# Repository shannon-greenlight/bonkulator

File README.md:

# Bonkulator
# The Bonkulator has been replaced by Thor's Arsenal

The Bonkulator is a Eurorack module that fits into a 3U x 14HP slot. It features 8 programmable outputs and 6 programmable inputs. The front-panel user controls consist of a 128×64 pixel 2-color OLED display, a rotary encoder for adjusting parameters and a button for each trigger and output.

# main_board, panel

These repos contain the materials needed to construct the Bonkulator main board and the front panel.
The files are for KiCAD 6.0. Go to the Greenlight Kicad repo to get the needed libraries.
The gerber files work with JLCPC and will most likely work with other board manufacturers.

Assembly instructions are in main_board\fab\bonkulator_assembly.docx.

When using the JLCPCB assembly service, the BOM is split into 3 parts.

- bom/lcsc/bonkulator_bom.xlsx : The parts to be assembled by JLCPCB
- bom/digi-key/bonkulator_bom.xlsx : The remaining parts to be assembled by user
- bom/other/other_bom.xlsx : The parts that must be bought from sources other than JLCPCB and Digi-Key

Also, when an assembly service is used, a component position file is required. This file's path is: fab/Bonkulator_cpl.xlsx

notes: The bom and cpl files are auto-generated from the csv BOM files produced by KiCAD. You will need to refresh the data when changes to the schematic that affect the BOM or changes to the board layout occur.
If they exist, the extra parts and additional data fields that appear on the schematic help to produce the different BOM files. They must be maintained for these BOMs to come out right.

# code

This repository contains the elements needed to build code for the Bonkulator.

# BonkDaddy

The Bonk Daddy is an addition to the Bonkulator that provides these benefits:

- Front Panel USB access
- Power sensing shuts off USB to Arduino when synth power is off
- Reset switch
- USB Power indicator
- Trig In indicators
- Boot Loader indicator
- Extremely useful to those who use Terminal Remote mode

The folder structure of the Bonk Daddy is similar to the Bonkulator Hardware folder, main_board. Currently there is no support for assembly service.

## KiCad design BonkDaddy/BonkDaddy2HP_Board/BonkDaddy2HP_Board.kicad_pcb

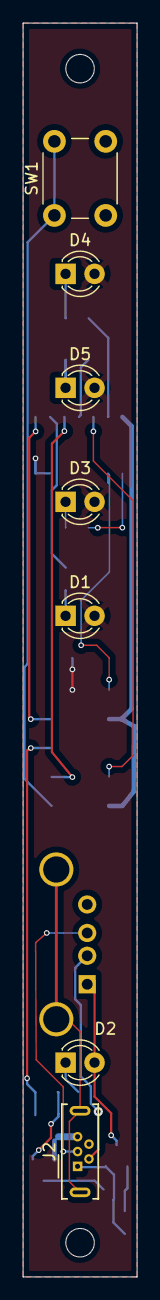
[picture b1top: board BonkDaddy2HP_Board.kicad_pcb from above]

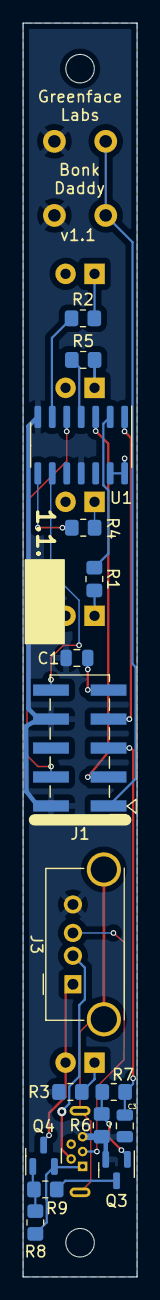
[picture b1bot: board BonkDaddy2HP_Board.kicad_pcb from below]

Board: 2 copper layers, 10.0 x 110.0 mm, 25 parts (16 on the bottom side), 25 nets.

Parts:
C1, C3: 1uF; C_0805_2012Metric
D1: RED LED; LED_D3.0mm
D2, D4: GREEN LED; LED_D3.0mm
D3: YELLOW LED; LED_D3.0mm
D5: BLUE LED; LED_D3.0mm
H1, H2: MountingHole; MountingHole_2.5mm
J1: EXP; PinHeader_2x05_P2.54mm_Vertical_SMD
J2: USB_B_Micro; USB_Micro-B_Wuerth_614105150721_Vertical
J3: USB_A; USB_A_Amphenol_UE27AE54100_Vertical
Q3: 2N7002; SOT-23
Q4: MMBT3906; SOT-23
R1, R2, R4, R5: 620; R_0805_2012Metric_Pad1.20x1.40mm_HandSolder
R3: 1K; R_0805_2012Metric_Pad1.20x1.40mm_HandSolder
R6, R9: 10K; R_0805_2012Metric_Pad1.20x1.40mm_HandSolder
R7, R8: 30K; R_0805_2012Metric_Pad1.20x1.40mm_HandSolder
SW1: Reset; SW_PUSH_6mm
U1: 74AHC14; SOIC-14_3.9x8.7mm_P1.27mm

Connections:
+3V3: C1.1, D1.2 (A), D3.2 (A), D4.2 (A), D5.2 (A), J1.9, U1.13, U1.14 (VCC)
+12V: C3.1, J1.5, R7.2
GND: C1.2, C3.2, J1.2, J1.8, J2.5 (GND), J3.4 (GND), Q3.2 (S), R3.1, R6.2, SW1.2, U1.7 (GND), U1.11
unnamed: D1.1 (K), R1.2
unnamed: D2.1 (K), R3.2
unnamed: D2.2 (A), J3.1 (VBUS), Q4.3 (C)
unnamed: D3.1 (K), R4.2
unnamed: D4.1 (K), R2.2
unnamed: D5.1 (K), R5.2
unnamed: J1.1, SW1.1
unnamed: J1.3, U1.3
unnamed: J1.4, U1.5
unnamed: J1.7, U1.1
unnamed: J1.10, U1.9
unnamed: J2.1 (VBUS), Q4.2 (E), R8.2
unnamed: J2.2 (D-), J3.2 (D-)
unnamed: J2.3 (D+), J3.3 (D+)
unnamed: J2.6 (Shield), J3.5 (Shield)
unnamed: Q3.1 (G), R6.1, R7.1
unnamed: Q3.3 (D), R9.1
unnamed: Q4.1 (B), R8.1, R9.2
unnamed: R1.1, U1.2
unnamed: R2.1, U1.6
unnamed: R4.1, U1.8
unnamed: R5.1, U1.4

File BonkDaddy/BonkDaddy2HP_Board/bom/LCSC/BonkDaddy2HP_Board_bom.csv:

"Designator","Comment","Footprint","JLCPCBPart#"
"C1, C3, ","1uF","Capacitor_SMD:C_0805_2012Metric","C28323"
"J1, ","EXP","Connector_PinHeader_2.54mm:PinHeader_2x05_P2.54mm_Vertical_SMD","C124391"
"J3, ","USB_A","sputterizer:USB_A_Amphenol_UE27AE54100_Vertical","C386737"
"Q3, ","2N7002","Package_TO_SOT_SMD:SOT-23","C8545"
"Q4, ","MMBT3906","Package_TO_SOT_SMD:SOT-23","C266589"
"R1, R2, R4, R5, ","620","Resistor_SMD:R_0805_2012Metric_Pad1.20x1.40mm_HandSolder","C17782"
"R3, ","1K","Resistor_SMD:R_0805_2012Metric_Pad1.20x1.40mm_HandSolder","C17513"
"R6, R9, ","10K","Resistor_SMD:R_0805_2012Metric_Pad1.20x1.40mm_HandSolder","C17414"
"R7, R8, ","30K","Resistor_SMD:R_0805_2012Metric_Pad1.20x1.40mm_HandSolder","C17621"
"U1, ","74AHC14","Package_SO:SOIC-14_3.9x8.7mm_P1.27mm","C5605"

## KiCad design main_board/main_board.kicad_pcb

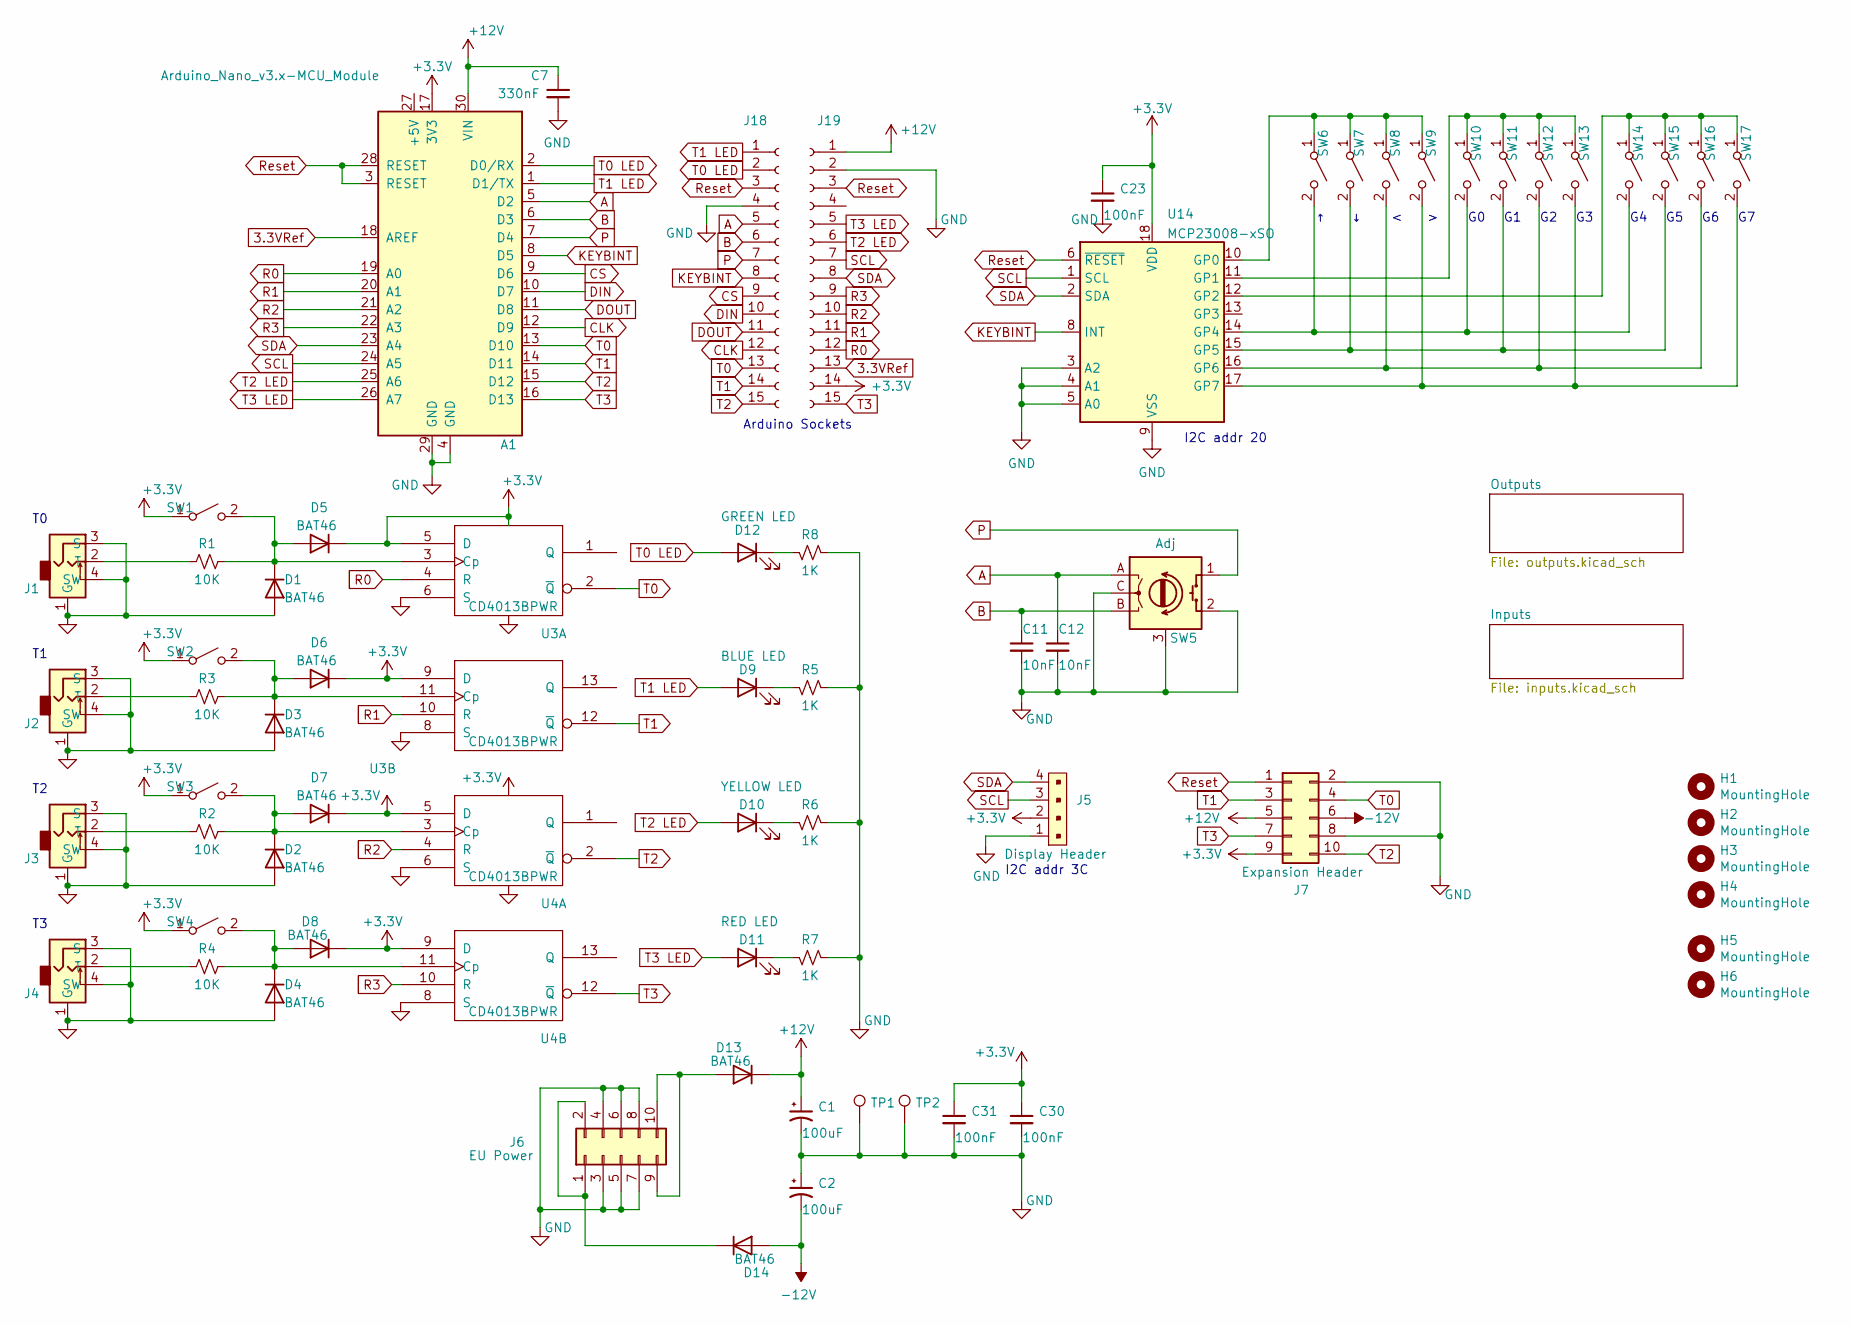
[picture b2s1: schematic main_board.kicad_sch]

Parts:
A1: Arduino_Nano_v3.x-MCU_Module; Arduino_Nano; Digi-Key Part 1050-ABX00053-ND
C1, C2: 100uF; CP_Elec_6.3x5.4_Nichicon; Digi-Key Part 399-EDH107M016A9GAACT-ND
C7: 330nF; C_0805_2012Metric_Pad1.18x1.45mm_HandSolder; Digi-Key Part 311-1888-1-ND
C11, C12: 10nF; C_0805_2012Metric_Pad1.18x1.45mm_HandSolder; Digi-Key Part 311-1136-1-ND
C23, C30, C31: 100nF; C_0805_2012Metric_Pad1.18x1.45mm_HandSolder; Digi-Key Part 478-10836-1-ND
D1, D2, D3, D4, D5, D6, D7, D8, D13, D14: BAT46; D_0805_2012Metric_Pad1.15x1.40mm_HandSolder; Digi-Key Part 478-7800-1-ND
D9: BLUE LED; LED_D3.0mm; Digi-Key Part 160-1035-ND
D10: YELLOW LED; LED_D3.0mm; Digi-Key Part 160-1035-ND
D11: RED LED; LED_D3.0mm; Digi-Key Part 160-1035-ND
D12: GREEN LED; LED_D3.0mm; Digi-Key Part 160-1035-ND
H1, H2, H3, H4: MountingHole; MountingHole_2.5mm
H5, H6: MountingHole; MountingHole_2.5mm-No-Margin
J1, J2, J3, J4: 3.5mm Jack; Molex-0472570001; Digi-Key Part WM17366-ND
J5: Display Header; OLED_Header_Slim; MPN 0022232041; Digi-Key Part SAM1011-04-ND
J6: EU Power; PinHeader_2x05_P2.54mm_Vertical; Digi-Key Part S2011EC-05-ND
J7: Expansion Header; PinHeader_2x05_P2.54mm_Vertical; Digi-Key Part S2011EC-05-ND
J18, J19: Conn_01x15_Female; ArduinoConnector; LCSC Part # C124408
R1, R2, R3, R4: 10K; R_0805_2012Metric_Pad1.20x1.40mm_HandSolder; Digi-Key Part 13-RC0805JR-1010KLCT-ND
R5, R6, R7, R8: 1K; R_0805_2012Metric_Pad1.20x1.40mm_HandSolder; Digi-Key Part 311-10KARCT-ND
SW1, SW2, SW3, SW4, SW6, SW7, SW8, SW9, SW10, SW11, SW12, SW13, SW14, SW15, SW16, SW17: Push Button; SW_PUSH_6mm; Digi-Key Part 450-1643-ND
SW5: Adj; Rotary_Encoder_Switched_PEC11R; Digi-Key Part 987-1187-ND
TP1, TP2: TestPoint; TestPoint_Keystone_5005-5009_Compact; Digi-Key Part 36-5006-ND
U3, U4: CD4013BPWR; TSSOP-14_4.4x5mm_P0.65mm; LCSC Part # C406860
U14: MCP23008-xSO; SOIC-18W_7.5x11.6mm_P1.27mm; Digi-Key Part MCP23008-E/SO-ND

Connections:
3.3VRef: A1.18 (AREF), J19.13; also elsewhere on the board
+3V3: A1.17 (3V3), C23.1, C30.1, C31.1, D5.1 (K), D6.1 (K), D7.1 (K), D8.1 (K), J5.2, J7.9, J19.14, SW1.1 (A), SW2.1 (A), SW3.1 (A), SW4.1 (A), U3.5 (D), U3.9 (D), U3.14 (Vdd), U4.5 (D), U4.9 (D), U4.14 (Vdd), U14.18 (VDD); also elsewhere on the board
+12V: A1.30 (VIN), C1.1, C7.1, D13.1 (K), J7.5, J19.1; also elsewhere on the board
-12V: C2.2, D14.2 (A), J7.6; also elsewhere on the board
A: A1.5 (D2), C12.1, J18.5, SW5.A
B: A1.6 (D3), C11.1, J18.6, SW5.B
CLK: A1.12 (D9), J18.12; also elsewhere on the board
CS: A1.9 (D6), J18.9; also elsewhere on the board
DIN: A1.10 (D7), J18.10; also elsewhere on the board
DOUT: A1.11 (D8), J18.11; also elsewhere on the board
GND: A1.4 (GND), A1.29 (GND), C1.2, C2.1, C7.2, C11.2, C12.2, C23.2, C30.2, C31.2, D1.2 (A), D2.2 (A), D3.2 (A), D4.2 (A), J1.1 (G), J1.3 (S), J1.4 (SW), J2.1 (G), J2.3 (S), J2.4 (SW), J3.1 (G), J3.3 (S), J3.4 (SW), J4.1 (G), J4.3 (S), J4.4 (SW), J5.1, J6.3, J6.4, J6.5, J6.6, J6.7, J6.8, J7.2, J7.8, J18.4, J19.2, R5.1, R6.1, R7.1, R8.1, SW5.2 (S2), SW5.3 (GND), SW5.C, TP1.1, TP2.1, U3.6 (S), U3.7 (Vss), U3.8 (S), U4.6 (S), U4.7 (Vss), U4.8 (S), U14.3 (A2), U14.4 (A1), U14.5 (A0), U14.9 (VSS); also elsewhere on the board
KEYBINT: A1.8 (D5), J18.8, U14.8 (INT)
unnamed: D1.1 (K), D5.2 (A), R1.1, SW1.2 (B), U3.3 (Cp)
unnamed: D2.1 (K), D7.2 (A), R2.1, SW3.2 (B), U4.3 (Cp)
unnamed: D3.1 (K), D6.2 (A), R3.1, SW2.2 (B), U3.11 (Cp)
unnamed: D4.1 (K), D8.2 (A), R4.1, SW4.2 (B), U4.11 (Cp)
unnamed: D9.1 (K), R5.2
unnamed: D10.1 (K), R6.2
unnamed: D11.1 (K), R7.2
unnamed: D12.1 (K), R8.2
unnamed: D13.2 (A), J6.9, J6.10
unnamed: D14.1 (K), J6.1, J6.2
unnamed: J1.2 (T), R1.2
unnamed: J2.2 (T), R3.2
unnamed: J3.2 (T), R2.2
unnamed: J4.2 (T), R4.2
unnamed: SW6.1 (A), SW7.1 (A), SW8.1 (A), SW9.1 (A), U14.10 (GP0)
unnamed: SW10.1 (A), SW11.1 (A), SW12.1 (A), SW13.1 (A), U14.11 (GP1)
unnamed: SW6.2 (B), SW10.2 (B), SW14.2 (B), U14.14 (GP4)
unnamed: SW7.2 (B), SW11.2 (B), SW15.2 (B), U14.15 (GP5)
unnamed: SW8.2 (B), SW12.2 (B), SW16.2 (B), U14.16 (GP6)
unnamed: SW9.2 (B), SW13.2 (B), SW17.2 (B), U14.17 (GP7)
unnamed: SW14.1 (A), SW15.1 (A), SW16.1 (A), SW17.1 (A), U14.12 (GP2)
P: A1.7 (D4), J18.7, SW5.1 (S1)
R0: A1.19 (A0), J19.12, U3.4 (R)
R1: A1.20 (A1), J19.11, U3.10 (R)
R2: A1.21 (A2), J19.10, U4.4 (R)
R3: A1.22 (A3), J19.9, U4.10 (R)
Reset: A1.3 (RESET), A1.28 (RESET), J7.1, J18.3, J19.3, U14.6 (~RESET); also elsewhere on the board
SCL: A1.24 (A5), J5.3, J19.7, U14.1 (SCL); also elsewhere on the board
SDA: A1.23 (A4), J5.4, J19.8, U14.2 (SDA); also elsewhere on the board
T0: A1.13 (D10), J7.4, J18.13, U3.2 (~Q)
T0 LED: A1.2 (D0/RX), D12.2 (A), J18.2
T1: A1.14 (D11), J7.3, J18.14, U3.12 (~Q)
T1 LED: A1.1 (D1/TX), D9.2 (A), J18.1
T2: A1.15 (D12), J7.10, J18.15, U4.2 (~Q)
T2 LED: A1.25 (A6), D10.2 (A), J19.6
T3: A1.16 (D13), J7.7, J19.15, U4.12 (~Q)
T3 LED: A1.26 (A7), D11.2 (A), J19.5

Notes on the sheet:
Arduino Sockets
I2C addr 3C
I2C addr 20

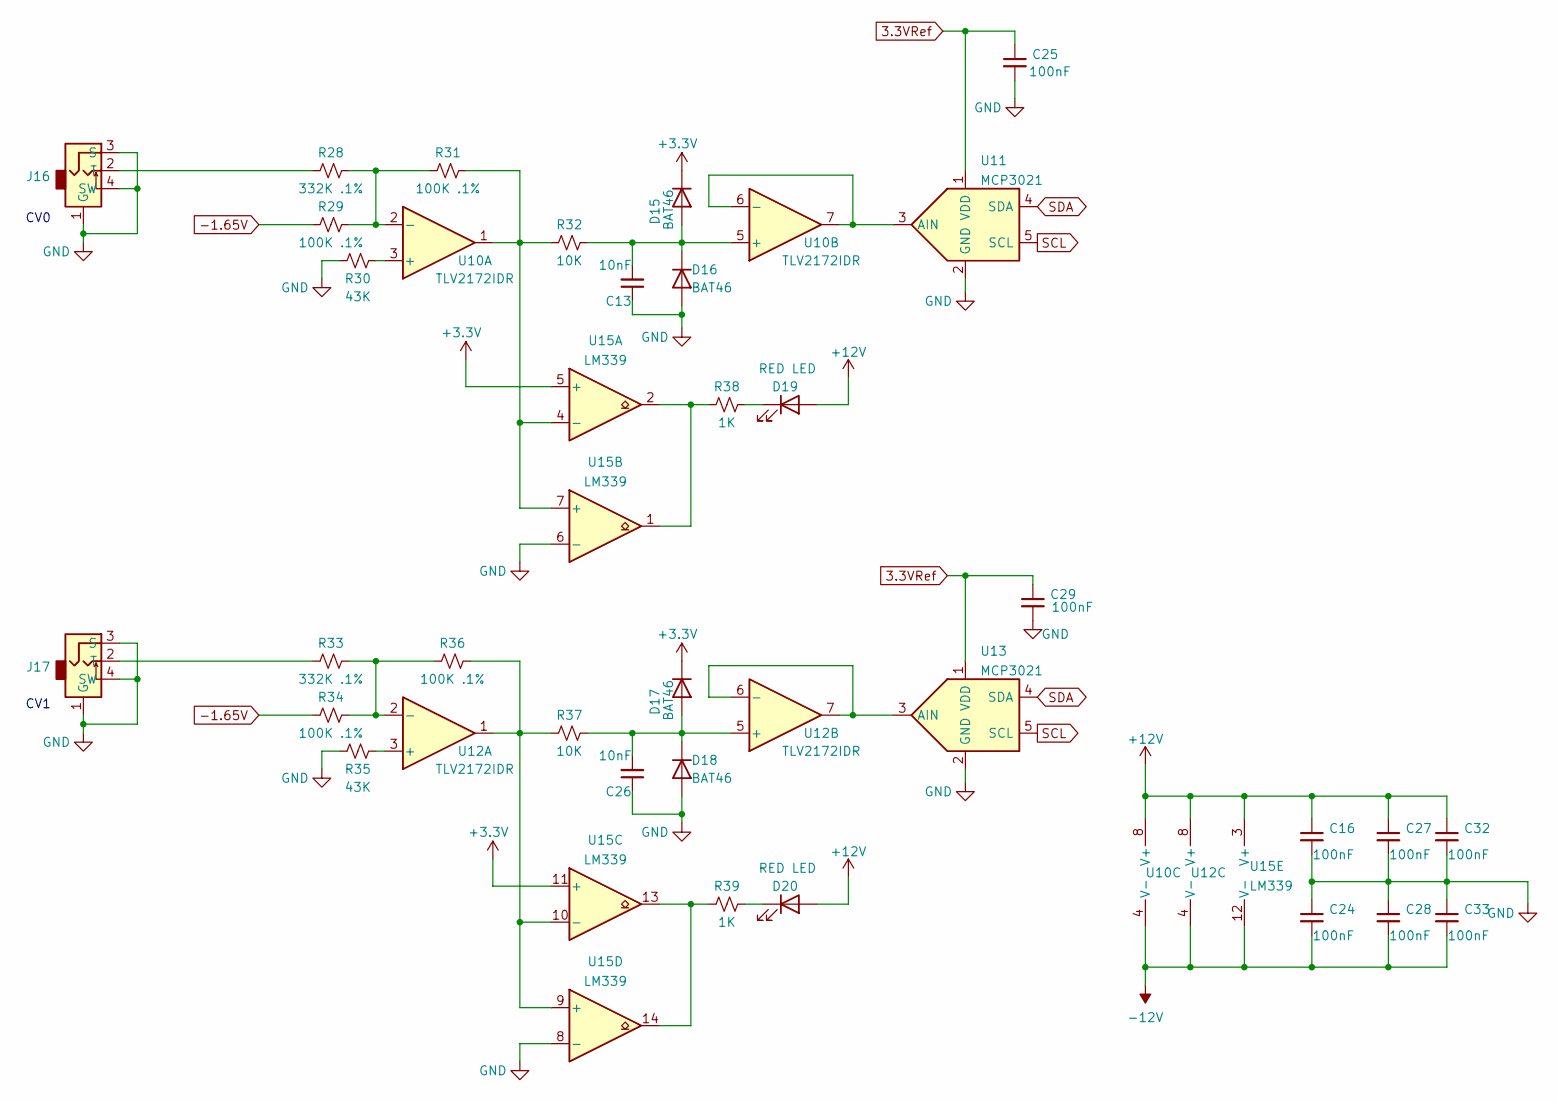
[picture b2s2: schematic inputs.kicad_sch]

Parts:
C13, C26: 10nF; C_0805_2012Metric_Pad1.18x1.45mm_HandSolder; Digi-Key Part 311-1136-1-ND
C16, C24, C25, C27, C28, C29, C32, C33: 100nF; C_0805_2012Metric_Pad1.18x1.45mm_HandSolder; Digi-Key Part 478-10836-1-ND
D15, D16, D17, D18: BAT46; D_0805_2012Metric_Pad1.15x1.40mm_HandSolder; Digi-Key Part 478-7800-1-ND
D19, D20: RED LED; LED_D3.0mm; Digi-Key Part 160-1035-ND
J16, J17: 3.5mm Jack; Molex-0472570001; Digi-Key Part WM17366-ND
R28, R33: 332K .1%; R_0805_2012Metric_Pad1.20x1.40mm_HandSolder; Digi-Key Part P332KDACT-ND
R29, R31, R34, R36: 100K .1%; R_0805_2012Metric_Pad1.20x1.40mm_HandSolder; Digi-Key Part YAG1759CT-ND
R30, R35: 43K; R_0805_2012Metric_Pad1.20x1.40mm_HandSolder; Digi-Key Part 311-43KARCT-ND
R32, R37: 10K; R_0805_2012Metric_Pad1.20x1.40mm_HandSolder; Digi-Key Part 13-RC0805JR-1010KLCT-ND
R38, R39: 1K; R_0805_2012Metric_Pad1.20x1.40mm_HandSolder; Digi-Key Part 311-10KARCT-ND
U10, U12: TLV2172IDR; SOIC-8-1EP_3.9x4.9mm_P1.27mm_EP2.29x3mm; Digi-Key Part 296-47385-1-ND
U11, U13: MCP3021; TSOT-23-5_HandSoldering; LCSC Part # C128576
U15: LM339; SOIC-14_3.9x8.7mm_P1.27mm; LCSC Part # C7948

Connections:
3.3VRef: C25.1, C29.1, U11.1 (VDD), U13.1 (VDD); also elsewhere on the board
+3V3: D15.1 (K), D17.1 (K), U15.5 (+), U15.11 (+); also elsewhere on the board
+12V: C16.1, C27.1, C32.1, D19.2 (A), D20.2 (A), U10.8 (V+), U12.8 (V+), U15.3 (V+); also elsewhere on the board
-1.65V: R29.2, R34.2; also elsewhere on the board
-12V: C24.2, C28.2, C33.2, U10.4 (V-), U12.4 (V-), U15.12 (V-); also elsewhere on the board
GND: C13.1, C16.2, C24.1, C25.2, C26.1, C27.2, C28.1, C29.2, C32.2, C33.1, D16.2 (A), D18.2 (A), J16.1 (G), J16.3 (S), J16.4 (SW), J17.1 (G), J17.3 (S), J17.4 (SW), R30.2, R35.2, U11.2 (GND), U13.2 (GND), U15.6 (-), U15.8 (-); also elsewhere on the board
unnamed: C13.2, D15.2 (A), D16.1 (K), R32.1, U10.5 (+)
unnamed: C26.2, D17.2 (A), D18.1 (K), R37.1, U12.5 (+)
unnamed: D19.1 (K), R38.2
unnamed: D20.1 (K), R39.2
unnamed: J16.2 (T), R28.2
unnamed: J17.2 (T), R33.2
unnamed: R28.1, R29.1, R31.2, U10.2 (-)
unnamed: R30.1, U10.3 (+)
unnamed: R31.1, R32.2, U10.1, U15.4 (-), U15.7 (+)
unnamed: R33.1, R34.1, R36.2, U12.2 (-)
unnamed: R35.1, U12.3 (+)
unnamed: R36.1, R37.2, U12.1, U15.9 (+), U15.10 (-)
unnamed: R38.1, U15.1, U15.2
unnamed: R39.1, U15.13, U15.14
unnamed: U10.6 (-), U10.7, U11.3 (AIN)
unnamed: U12.6 (-), U12.7, U13.3 (AIN)
SCL: U11.5 (SCL), U13.5 (SCL); also elsewhere on the board
SDA: U11.4 (SDA), U13.4 (SDA); also elsewhere on the board

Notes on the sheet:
CV0
CV1

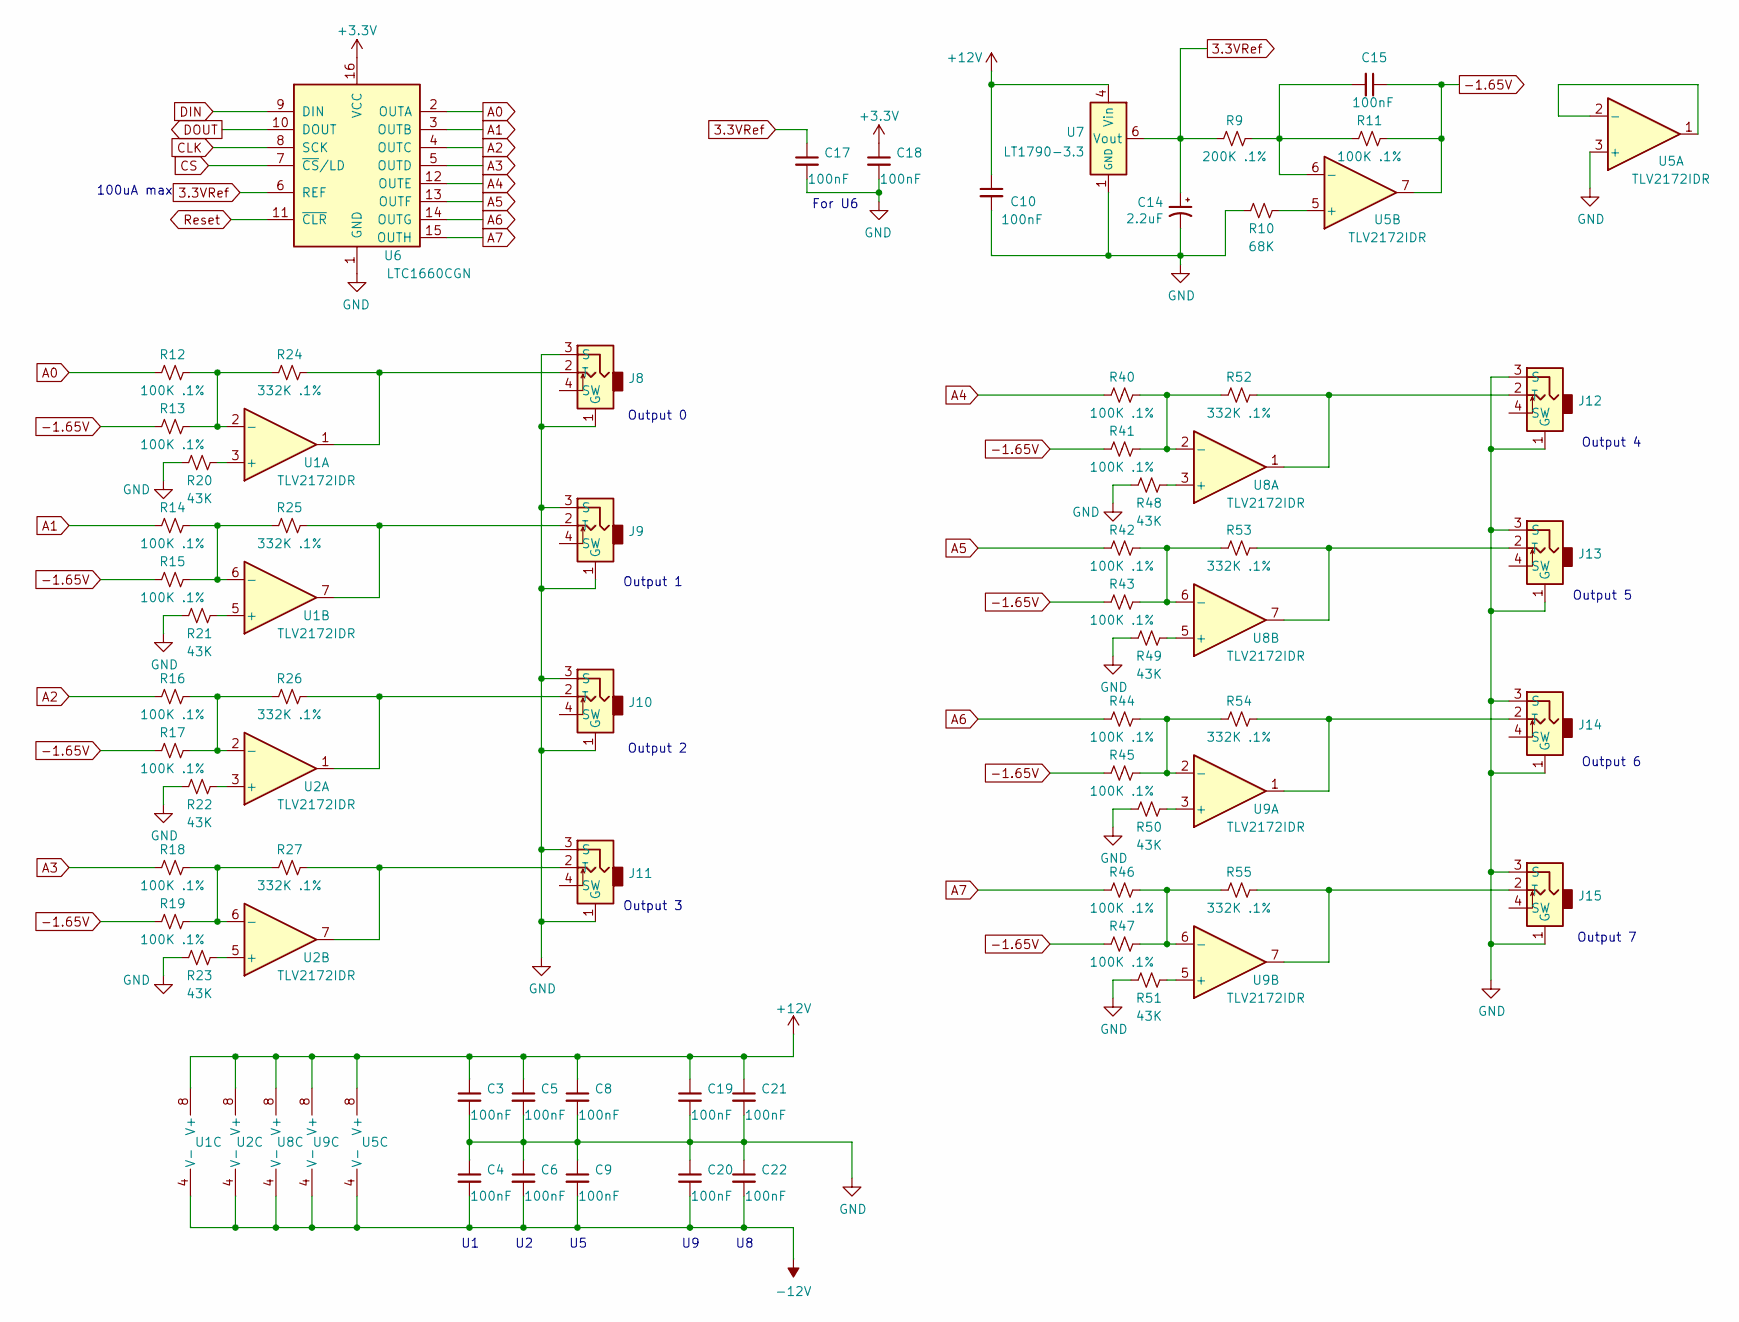
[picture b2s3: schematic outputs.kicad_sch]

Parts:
C3, C4, C5, C6, C8, C9, C10, C15, C17, C18, C19, C20, C21, C22: 100nF; C_0805_2012Metric_Pad1.18x1.45mm_HandSolder; Digi-Key Part 478-10836-1-ND
C14: 2.2uF; CP_EIA-2012-15_AVX-P; Digi-Key Part 478-3262-1-ND
J8, J9, J10, J11, J12, J13, J14, J15: 3.5mm Jack; Molex-0472570001; Digi-Key Part WM17366-ND
R9: 200K .1%; R_0805_2012Metric_Pad1.20x1.40mm_HandSolder; Digi-Key Part P200KDACT-ND
R10: 68K; R_0805_2012Metric_Pad1.20x1.40mm_HandSolder; Digi-Key Part 311-68KARCT-ND
R11, R12, R13, R14, R15, R16, R17, R18, R19, R40, R41, R42, R43, R44, R45, R46, R47: 100K .1%; R_0805_2012Metric_Pad1.20x1.40mm_HandSolder; Digi-Key Part YAG1759CT-ND
R20, R21, R22, R23, R48, R49, R50, R51: 43K; R_0805_2012Metric_Pad1.20x1.40mm_HandSolder; Digi-Key Part 311-43KARCT-ND
R24, R25, R26, R27, R52, R53, R54, R55: 332K .1%; R_0805_2012Metric_Pad1.20x1.40mm_HandSolder; Digi-Key Part P332KDACT-ND
U1, U2, U5, U8, U9: TLV2172IDR; SOIC-8-1EP_3.9x4.9mm_P1.27mm_EP2.29x3mm; Digi-Key Part 296-47385-1-ND
U6: LTC1660CGN; TSSOP-16-1EP_4.4x5mm_P0.65mm; Digi-Key Part LTC1660CGN#TRPBFCT-ND
U7: LT1790-3.3; TSOT-23-6; Digi-Key Part LT1790ACS6-3.3#TRMPBFCT-ND

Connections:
3.3VRef: C14.1, C17.1, R9.2, U6.6 (REF), U7.6 (Vout); also elsewhere on the board
+3V3: C18.1, U6.16 (VCC); also elsewhere on the board
+12V: C3.1, C5.1, C8.1, C10.1, C19.1, C21.1, U1.8 (V+), U2.8 (V+), U5.8 (V+), U7.4 (Vin), U8.8 (V+), U9.8 (V+); also elsewhere on the board
-1.65V: C15.1, R11.1, R13.2, R15.2, R17.2, R19.2, R41.2, R43.2, R45.2, R47.2, U5.7; also elsewhere on the board
-12V: C4.2, C6.2, C9.2, C20.2, C22.2, U1.4 (V-), U2.4 (V-), U5.4 (V-), U8.4 (V-), U9.4 (V-); also elsewhere on the board
A0: R12.2, U6.2 (OUTA)
A1: R14.2, U6.3 (OUTB)
A2: R16.2, U6.4 (OUTC)
A3: R18.2, U6.5 (OUTD)
A4: R40.2, U6.12 (OUTE)
A5: R42.2, U6.13 (OUTF)
A6: R44.2, U6.14 (OUTG)
A7: R46.2, U6.15 (OUTH)
CLK: U6.8 (SCK); also elsewhere on the board
CS: U6.7 (~CS/LD); also elsewhere on the board
DIN: U6.9 (DIN); also elsewhere on the board
DOUT: U6.10 (DOUT); also elsewhere on the board
GND: C3.2, C4.1, C5.2, C6.1, C8.2, C9.1, C10.2, C14.2, C17.2, C18.2, C19.2, C20.1, C21.2, C22.1, J8.1 (G), J8.3 (S), J9.1 (G), J9.3 (S), J10.1 (G), J10.3 (S), J11.1 (G), J11.3 (S), J12.1 (G), J12.3 (S), J13.1 (G), J13.3 (S), J14.1 (G), J14.3 (S), J15.1 (G), J15.3 (S), R10.2, R20.2, R21.2, R22.2, R23.2, R48.2, R49.2, R50.2, R51.2, U5.3 (+), U6.1 (GND), U7.1 (GND), U7.2 (GND); also elsewhere on the board
unnamed: C15.2, R9.1, R11.2, U5.6 (-)
unnamed: J8.2 (T), R24.1, U1.1
unnamed: J9.2 (T), R25.1, U1.7
unnamed: J10.2 (T), R26.1, U2.1
unnamed: J11.2 (T), R27.1, U2.7
unnamed: J12.2 (T), R52.1, U8.1
unnamed: J13.2 (T), R53.1, U8.7
unnamed: J14.2 (T), R54.1, U9.1
unnamed: J15.2 (T), R55.1, U9.7
unnamed: R10.1, U5.5 (+)
unnamed: R12.1, R13.1, R24.2, U1.2 (-)
unnamed: R14.1, R15.1, R25.2, U1.6 (-)
unnamed: R16.1, R17.1, R26.2, U2.2 (-)
unnamed: R18.1, R19.1, R27.2, U2.6 (-)
unnamed: R20.1, U1.3 (+)
unnamed: R21.1, U1.5 (+)
unnamed: R22.1, U2.3 (+)
unnamed: R23.1, U2.5 (+)
unnamed: R40.1, R41.1, R52.2, U8.2 (-)
unnamed: R42.1, R43.1, R53.2, U8.6 (-)
unnamed: R44.1, R45.1, R54.2, U9.2 (-)
unnamed: R46.1, R47.1, R55.2, U9.6 (-)
unnamed: R48.1, U8.3 (+)
unnamed: R49.1, U8.5 (+)
unnamed: R50.1, U9.3 (+)
unnamed: R51.1, U9.5 (+)
unnamed: U5.1, U5.2 (-)
Reset: U6.11 (~CLR); also elsewhere on the board

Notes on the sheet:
100uA max
Output 3
For U6
Output 6
Output 5
Output 1
Output 7
Output 2
Output 0
Output 4

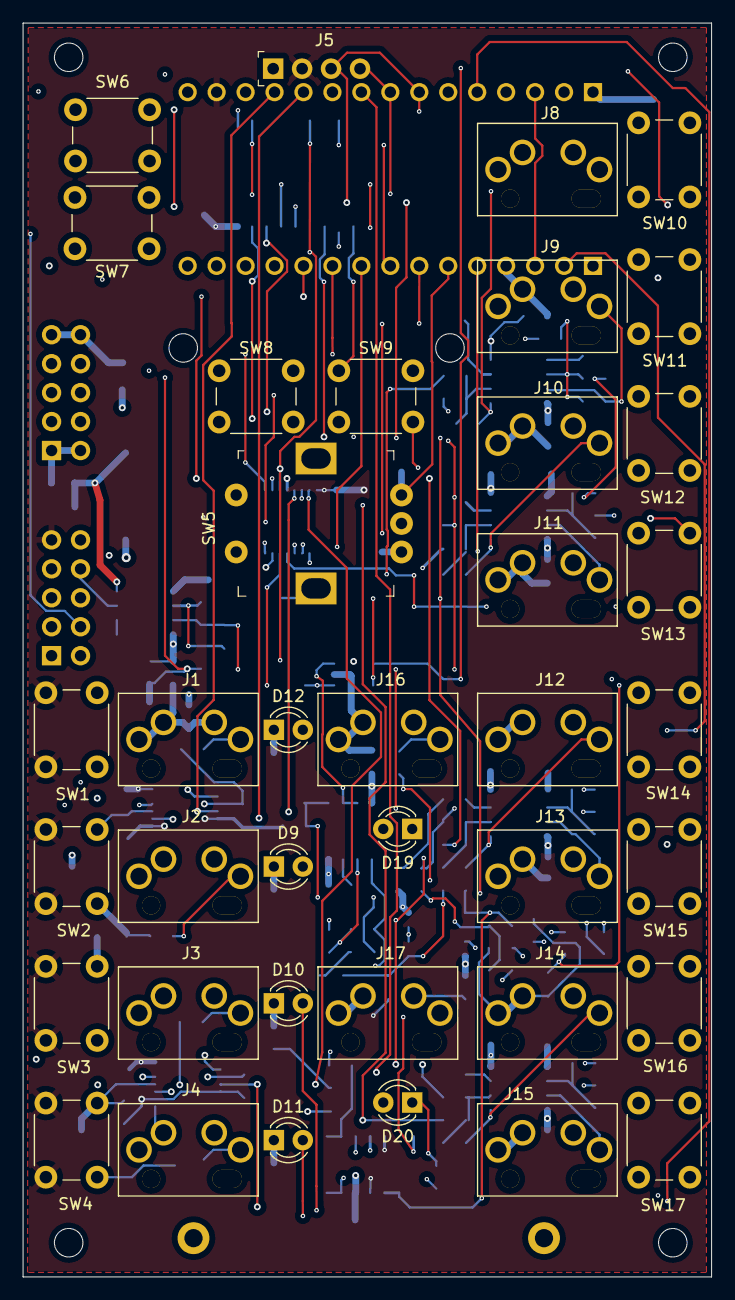
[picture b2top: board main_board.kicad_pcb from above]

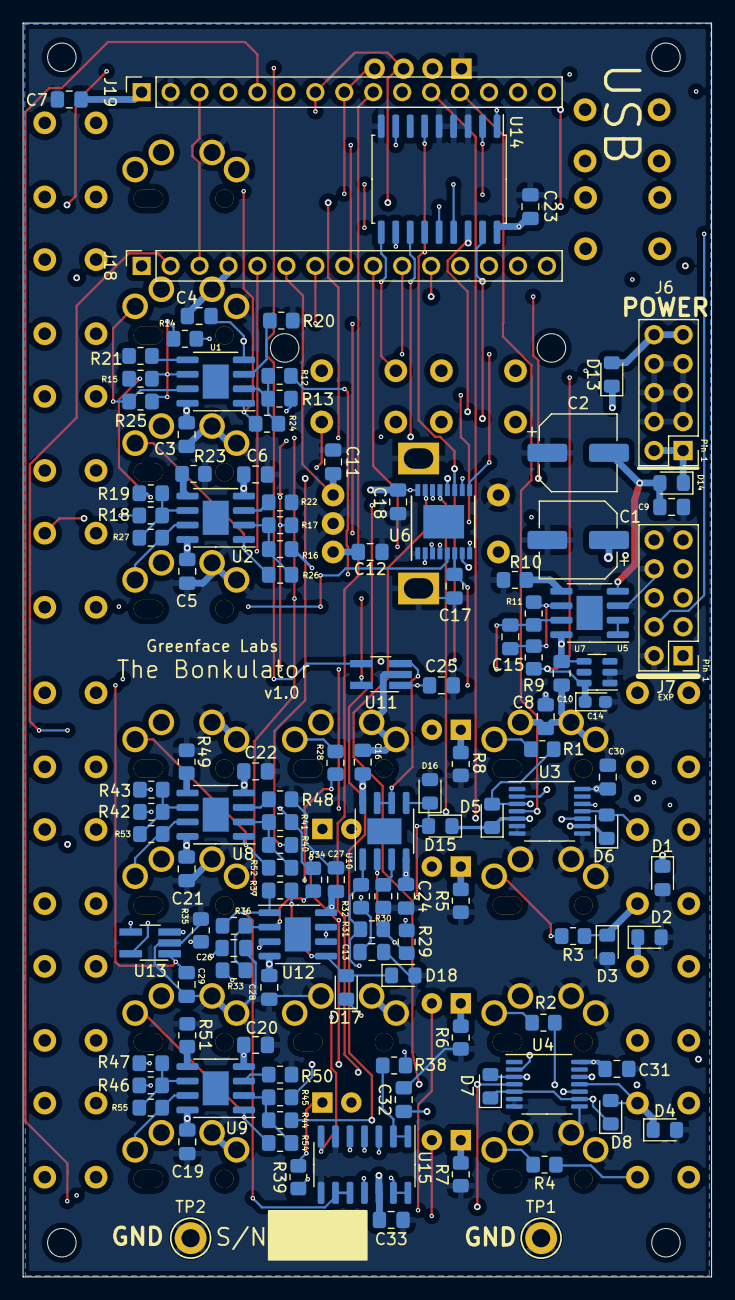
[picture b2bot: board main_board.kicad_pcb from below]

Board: 4 copper layers, 60.4 x 110.0 mm, 167 parts (123 on the bottom side), 101 nets.

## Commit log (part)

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2022-02-17 Init check-in
2022-03-31 Ver 2.0 of board.
    Also major advances in code.
2022-07-27 Version 0.03
2022-08-11 Version .06
2022-08-20 Version .09
2022-09-05 Version .20
    Moves to external library
2022-09-11 Moves common files to library
2022-09-28 Software v2.2
    Removes unneeded files.
    Adds pre-flight handler in WiFi do_server();
    Removes debug printouts.
2022-09-28 Delete arduino_secrets.h
    Removes secrets folder
2022-09-29 Updates panel
2022-10-01 Updates monitor circuitry. Sets outputs on init().
2022-10-06 Version .25
    Fixes CV mod of period.
2022-10-11 Update to manual
2022-10-15 Adds Bonk Daddy
2022-10-21 Upgrades board to v5. Adds Bonk Daddy.
2022-10-22 Moves gerber to fab folder.
2022-10-22 Project cleanup
    Removes dev files
2022-11-02 Adds 2HP BonkDaddy. Fixes boms/cpl. Updates Readme
2022-11-06 Getting ready for first major release.
    Adds support for main board v5. Output range adjustment.
    Makes DAC use all 12 bits.
2022-11-09 Reset parameters via web doesn't cut connection
2022-11-09 Adds release binaries
2022-11-10 Adds USB connector to Bonk Daddy 2HP LCSC bom
2022-11-16 Adds debug message to wifi_ui.h
2022-11-16 LED current resistors now 2,.2K
2022-11-19 New waveform structure
    Removes inverse waveforms, adds haystack and pyramid waveforms.
    Fixes Pulse waveform.
    Renames "Period" to "Active Time", "Post Delay" to "Idle Time".
    Extends parameters to use all 16 bits. (Active Time max is now 65535)
2022-11-21 Adds debounce caps to trigger inputs
2022-11-21 Sets code to version 2.0.0
2022-11-23 Fixes idle value CV.
    Now matches 12 bit output resolution
2022-12-03 Updates main board to 4.1, fixes panel LED that was off center.
2022-12-05 Fix for rotary encoder
2022-12-06 v2.1.1
    Adds trigger hold_off
2022-12-07 Updates manual
    Adds trigger hold_off section
2022-12-09 Update Rotary_Encoder_fxns.h
    Fixes warning about signed - unsigned comparison
2022-12-09 Moves hardware define to the defines file.
2022-12-09 Adds trigger skip and density
2022-12-10 Update BONK_output_fxns.h
    Makes external clock amendment happen at the correct time.
2022-12-10 Update settings_fxns.h
    Doesn't save WiFi setting anymore. It needs to init this val to OFF when resetting to factory defaults.
2022-12-10 Update trigger_fxns.h
    Terminal status correctly prints External clock settings now.
2022-12-10 Update Bonkulator.ino
    Fixes init_all so that parameters are correctly transferred after init.
2022-12-10 Release of v2.2.0
2022-12-13 Update main_board.pdf
    Adds debounce caps
2022-12-19 Update output_cal_fxns.h
    Changes comment
2022-12-19 Update TRIGGER.cpp
    Fixes trigger. Needed break statement!
2022-12-19 release of v2.2.2
2022-12-19 Adds debounce caps to trigger switches
2023-02-02 Adds CV Trigger
    Generates a trigger when CV input changes.
2023-02-02 Fixes Settings bug
    Needed to save selected_fxn before using it in begin()
2023-04-15 Fixes remote trigger commands and idle value for unipolar operation
2023-05-08 Makes Idle Value a fixed point variable
2023-05-19 Uses actual values for Idle Value init, offset, and max instead of ideal values
2023-05-19 Shortens names of user waveforms.
    Prevents memory err in sending data to WiFi client.
2023-05-19 Handles decimal point and offset in send_data_to_client
2023-05-19 Fixes warning about unsigned vs signed comparison
2023-05-19 Adds = command to set DAC directly
2023-05-26 Update BONK_output_fxns.h
    Removes scale correction from set idle value.
    Creates fxn: scale_dac.
2023-05-26 Adds quantize_value stub.
2023-05-26 Some debug stuff for Quantize fxn.
2023-05-28 Adds space in status string to make room for WiFi bars
2023-05-29 Updates to terminal_print_status
    Deletes global status_string and passes string to fxn now.
    WiFi bars are now handled using value sent to display.
2023-05-31 Adds dac_vdc, makes scale_dac take float as input
2023-06-03 Update BONK_output_fxns.h
    Idle Value is not scaled. It uses actual max instead of theoretical max.
2023-06-03 Fixes apply scale and offset.
2023-06-04 Update output_cal_fxns.h
    Sets +/-5V range. Uses 5V for calibrating scale.
2023-06-04 Partial work on quantize. Commented out.
2023-06-05 Version 2.3.5 of code
2023-06-08 Uses generate_boms.bat now.
2023-06-08 Updates main_board, uses generate_boms.bat
    Updates reverse protection circuitry on main board.
    Updates 3.3V reference circuitry.
    Uses generate_boms and retires .xlsx BOM files.
2023-07-24 Updates BONKULATOR REMOTE COMMANDS section
2023-07-24 Not sure what this change is about. Looks like a view change.
2023-07-24 Change comment and debug method
2023-07-24 Adds lib path
2023-07-24 Adds USB Direct mode.
2023-07-26 Press Activate to Push Activate so it fits on OLED
2023-07-26 Fix USB Direct when sending refresh cmd.
2023-07-26 Removes extraneous spaces in labels
2023-07-26 New version: v2.4.1
2023-07-26 When setting wifi message, don't randomize waveform if user wave.
2023-07-27 Removes leading spaces from labels
2023-07-27 Adds init wave to user waveforms
2023-07-27 Version v2.4.2
2023-08-07 Rev 4.2 of board
2023-08-07 USB Direct
2023-08-11 Adds set_cv_alt_values()
    Shows when CV takes over param.
2023-08-11 Adds wifi_toJSON()
    Doesn't send WiFi params to USB.
2023-08-11 Sets USB Direct to off on boot.
    Adds needed fxn stubs.
2023-08-11 Output display added to update_cv
    Correctly displays CV in param field after setting.
2023-08-11 Adds recv_user_waveform(in_str)
2023-08-11 Just in case.
    Alternate definition for bool in_wifi()
2023-08-11 Adds user_waveforms_put_val()
2023-08-11 Adds recv_user_waveform()
2023-08-11 Accepts in_str up to 20 length.
    Fixes recv_user_waveform()
2023-08-12 Supports both CVs assigned to same parameter
2023-08-15 Fixes string entry being wrecked by terminal_print_status
2023-08-15 String entry shows on param now.
2023-08-23 backs up cp2 now.
2023-08-23 Adds send status for triggers
2023-08-28 Updates board to 5.0
    Adds output resistors. Fixes AS431 pinout
2023-08-28 Support for new board
    Adds Board Revision selection to settings. Removes need for scaling. Leaves scaling code intact just in case.
2023-09-02 Adds * to output label when uncalibrated.
    For reports to remote apps.
2023-09-02 Always send fxns to remote apps.
2023-09-14 Consolidates sending to USB and WiFi
2023-09-14 Adds send_data_to_USB, check_output_cal.
2023-09-14 Adds instructions for remote and status string.
2023-09-14 Adds WiFi Reset
2023-09-14 Changes wifi_ui_message to waveform_values
2023-09-27 Fixes redeclaration of #define
2023-09-27 Deletes unused temp variables.
2023-09-27 Ignores checkin_comment.txt
2023-09-27 For v3.0.0
2023-09-27 Removes KiCAD logo, moves display outline
2023-10-01 Fixes CV labels
2023-10-01 Version 3.0.1
2023-10-03 New front panel silkscreen
2023-10-03 Either Way doesn't work
    Saved just in case
2023-10-04 Updates to USB Direct text
2023-10-04 Goes to diodes for reverse power protection
    Re-layout for better noise performance.
2023-10-21 Test release. 3.0.4
2023-10-22 Fixes trigger LED
2023-10-22 Fixes keyboard bug
    Doing a digitalRead on A2 causes input not to go to zero.
    Using analogRead fixes this.
2023-10-22 Fixes keyboard bug
    Using digitalRead on A2 causes inpuit not to go to zero.
    Using analogRead fixes this.
2023-10-22 Added comment
2023-10-22 ignore comment.txt
2023-10-24 Don't send offset correction with wave data. Not needed.
2023-10-24 Remove comment
2023-10-24 Ignore this file
2023-10-30 Change name of output to channel for triggers.
    Triggers now trigger inputs.
2023-10-30 Adds Bounce support
    Change name of output to channel for triggers.
2023-10-30 Adds Bounce fxn.
2023-10-30 Moves adc scale factor here from input_cal
2023-10-30 Moves scale factor to hardware fxns.
2023-10-30 Changes trigger output name to channel
2023-10-30 Creates check_bounce()
2023-10-31 Corrects copy of bonk_cp app code.
2023-10-31 Moves bounce calc to bounce_fxns
2023-10-31 Work on Bounce
    Removes CV params.
    Makes scale and offset params use offsets. Now bipolar range.
    Moves calc code from Bonkulator.ino
    Calculates bounce correctly.
2023-10-31 Ignores added.
2023-11-02 Makes system message persist. For Bounce.
2023-11-02 Adds Bounce support for sensing and sending status.
2023-11-02 Improves check_bounce. Adds check_bounce_triggers and reset_inputs.
2023-11-02 Uses define instead of 2048
2023-11-02 Adds bounce support to trigger fxns in process_cmd.
2023-11-02 Adds support for Bounce
2023-11-02 Adds bounce to trigger report.
2023-11-03 Prints reading to OLED and terminal.
    Also uses one copy of bounce_labels
2023-11-03 Supports sliders in bounce fxn.
2023-11-04 Release of 3.1.0
2023-11-11 Fixes to Bounce fxn.
2023-11-11 Adds instructions for libraries.
2023-11-11 Fixes path to secrets.h
2023-11-11 Trivial change tests Mac
2023-11-11 Adds example secrets folder
2023-11-11 Removes duplicate entries.
2023-11-11 New layout. Fixes regulator chip pinout error.
2023-11-12 Bounce additions
2023-11-15 Fixes failure to trigger on boot.
    You used to have to go to the desired output before it would trigger properly.
2023-12-02 Updates code to work on Mac.
2023-12-02 Now user selects a number.
2023-12-02 makes executable
2023-12-02 Adds download of arduino-cli if it doesn't exist
2023-12-03 Create arduino-cli
    For the Mac
2023-12-03 Uses arduino-cli to list boards.
2023-12-03 Specific test for Spankulator.
2023-12-03 Only bumps index on valid boards.
2023-12-03 Removes verbose
    Edited by Mac
2023-12-04 Fixes Mac upload
    User no longer needs to chmod and use sed to prepare release.
2023-12-05 Uses arduino-cli to compile.
    Removes unneeded cache folder
2023-12-05 Make executable.
2023-12-05 Make it work like the batch file works.
2023-12-05 Moves #! to line 1
2023-12-06 Uses variable %product_name%
2023-12-07 Adds info on new additions for Mac.
2023-12-07 load_recent.sh calls list_ports.sh
2023-12-07 Fixes ask release number logic.
2023-12-07 Fixes tar args.
2023-12-07 Env var replaced with release.txt
2023-12-07 Adds 7z.exe instead of depending on install
2023-12-07 Updates code info. Moves it to the code folder.
2023-12-07 Fixes typo.
2023-12-08 Times the make process and prints results in hh:mm:ss format
2023-12-08 Adds text: (x to exit)
2024-01-08 Adds releases
2024-01-08 Fixes app crash
    Fixes crash in the app when you press a key to restore the display after it has entered screen-saver mode then send a command via the app.
2024-01-08 Updated LED resistors
2024-01-08 Adds split and full to BOMs
2024-01-08 Adds local libraries
2024-01-08 Disables squiggles
2024-01-08 Release 3.2.6
2024-01-08 Fixes main board.
    Fixes regulator footprint. Re lays out board to improve noise performance. Around -50db now at outputs.
2024-01-09 Updates bom for digi-key
2024-04-04 Fixes bounce function.
    Also stops repeat trigger when altering params.
2024-04-04 Change to triggering.
    Now re-triggers instead of toggling trigger.
2024-04-04 Adds drc exclusions.
2024-04-28 Removes unneeded space from string param.
2024-04-28 Sends group info to USB
    Instead of bounce info. Adding group without removing bounce exceeded data capabilities.
2024-04-28 Adds group variables.
2024-04-28 Adds put_group
2024-04-28 Fixes bug where yes couldn't be set to no by put_param
    input_offsets array was missing last element.
    Removed spaces from variables.
    Used F macro to reduce RAM usage.
2024-04-28 Adds group commands
    put_group and group_active added
    Affects Offset, Scale, and Randomness.
    Maybe do more next time.
2024-04-28 Version 3.4.1
2024-04-28 Adds section on grouping.
2024-05-06 Uses new backit and changes
2024-05-06 Release 3.5.0
2024-05-06 Adds ability to send value while sliding sliders.
    Also sends software version to remote.
2024-05-06 Adds section on Power installation and one on groups.
2024-05-06 Adds ability to send data while sliding sliders.
    Also checks software rev of Bonkulator to insure compatibility.
2024-05-08 Adds libraries
2024-05-11 Removes backit related files.
